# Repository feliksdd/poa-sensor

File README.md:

# POA-Sensor

Kabelgebundener Einstrahlungssensor mit KXOB25-14X1F-Referenzzelle, Präzisionsshunt, Zelltemperaturmessung und ADS1115. Ein Sensor wird über maximal 3 m Kabel von einem [PanelLog](https://github.com/feliksdd/panellog) versorgt und per I²C ausgelesen. Der Sensor wird parallel zur PV-Modulebene und möglichst unverschattet montiert.

| Datei | Inhalt |
|---|---|
| [KiCad-Projekt](hardware/poa-sensor.kicad_pro) · [Schaltplan](hardware/poa-sensor.kicad_sch) | Elektrische Quelle |
| [PCB](hardware/poa-sensor.kicad_pcb) | Layout mit Kradex-Kontur und integrierter Herstellerzeichnung |
| [PDF](hardware/poa-sensor.pdf) · [SVG](hardware/poa-sensor.svg) | Aktuelle Schaltplanansichten |
| [Stückliste](bom/bom.csv) | Bauteile, Bestellnummern und DNP-Bestückung |
| [Schaltung und Auslegung](docs/schaltung.md) | Messkanäle, Versorgung und I²C-Schnittstelle |
| [Mechanischer Aufbau](docs/aufbau.md) | Gehäusekontur, Zellkontakt und Montage |
| [Fertigung](docs/fertigung.md) | Bestückung und Fertigungsstand |

Das Schaltbild verwendet direkt gezeichnete Signalverbindungen, Spannungssymbole und zusammenhängende Funktionsgruppen. Das KiCad-Projekt verwendet KiCad 10. Die vorhandene PanelLog-Schnittstelle bleibt unverändert; eine eigene MCU oder Firmware ist nicht erforderlich.

Das PCB ist für **Kradex ZP60.60.40UJpH TM PC** mit transparentem Deckel angelegt. Das Layout enthält Leiterbahnen und konturgleiche GND-Flächen auf Ober- und Unterseite. Vor der Fertigung sind die offenen Punkte aus der Layoutprüfung zu klären. Herstellerzeichnungen, Freistellungen und Montagehöhe sind in [aufbau.md](docs/aufbau.md) beschrieben.

## Messprinzip und Umrechnung

Die KXOB25-14X1F arbeitet mit dem parallel geschalteten **1-Ω-Shunt RSH1** nahe am Kurzschluss. Auf diesem flachen Abschnitt der Zellkennlinie steigt der Strom näherungsweise proportional zur Einstrahlung in der Modulebene. Der ADS1115 misst die Shuntspannung differenziell an **AIN0–AIN1** mit getrennten Abgriffen an den beiden Shuntpads. Es gilt $I_\mathrm{Zelle} = U_\mathrm{SH}/R_\mathrm{SH}$. Bei einem PGA-Bereich von ±256 mV entspricht ein ADC-Count 7,8125 µV.

Bei 1.000 W/m², 25 °C und AM1.5 gibt ANYSOLAR typisch 58,6 mA Kurzschlussstrom an. Das entspricht am Shunt näherungsweise 58,6 mV bzw. 7.501 Counts. Aus dem typischen Temperaturkoeffizienten von +26,5 µA/K folgt die relative Korrektur $\alpha \approx 0{,}000452\,\mathrm{K}^{-1}$. [Datenblatt der KXOB25-14X1F](https://www.digikey.com/htmldatasheets/production/3648849/0/0/1/kxob25-14x1f-tr.pdf)

$$
G_\mathrm{POA} \approx 1000\,\frac{\mathrm W}{\mathrm{m^2}}\,
\frac{U_\mathrm{SH}-U_0}{58{,}6\,\mathrm{mV}}\,
\frac{1}{1+\alpha(T_\mathrm{Zelle}-25\,{}^\circ\mathrm C)}
$$

$U_0$ ist der bei lichtdicht abgedeckter Referenzzelle gemessene Offset. $T_\mathrm{Zelle}$ stammt vom NTC an der Zellrückseite. Eine offsetbereinigte Shuntspannung von 35,16 mV entspricht nominal 600 W/m² bei 25 °C bzw. 591 W/m² bei 60 °C.

Für absolute Werte den fertig montierten Sensor **mit Deckel** kalibrieren. Zuerst den Dunkeloffset $n_0$ in ADC-Counts erfassen. Dann bei stabiler Einstrahlung gleichzeitig den Sensorwert $n_\mathrm{ref}$, seine Zelltemperatur $T_\mathrm{ref}$ und die Einstrahlung $G_\mathrm{ref}$ einer kalibrierten Silizium-Referenzzelle messen. Beide Sensoren liegen in derselben Ebene. Die individuelle Empfindlichkeit ist

$$
S_{25} = \frac{n_\mathrm{ref}-n_0}{G_\mathrm{ref}\,[1+\alpha(T_\mathrm{ref}-25\,{}^\circ\mathrm C)]}
\quad \text{in Counts pro W/m².}
$$

Für die Auswertung in PanelLog gilt $G_\mathrm{POA}=(n-n_0)/(S_{25}[1+\alpha(T_\mathrm{Zelle}-25\,{}^\circ\mathrm C)])$. So gehen Zellstreuung, Shunt, ADC-Verstärkung und Deckeltransmission bei der Kalibriergeometrie in den Faktor ein. Den Einfluss des Deckels bei schrägem Lichteinfall separat durch Vergleichsmessungen prüfen. [Messkanäle und NTC-Auswertung](docs/schaltung.md)

## Werkzeuge

`bash tools/check_hardware.sh` prüft ERC, Netzliste und Stückliste. Die Ausgaben liegen in `build/kicad/` und werden nicht versioniert. `bash tools/export_schematic.sh` aktualisiert die PDF-/SVG-Ansichten unter `hardware/`.

Die verbindlichen Regeln für weitere Arbeiten stehen in [AGENTS.md](AGENTS.md).

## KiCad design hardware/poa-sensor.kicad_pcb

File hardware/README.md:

# Aktuelle Hardware: kabelgebundener POA, Revision 0.3

`poa-sensor.kicad_pro` / `poa-sensor.kicad_sch` sind das aktive Projekt: Referenzzelle, Shunt, Zell-NTC und I²C-ADC. Kabel und Versorgung sind in [architecture.md](../docs/architecture.md) festgelegt. Projektlokale Symbole einschließlich der festgelegten R/C-Kopien und Spannungssymbole vermeiden unterschiedliche Symbolbibliotheken zwischen KiCad 9 und 10; Footprints verweisen auf Standardbibliotheken bzw. `POA`.

Die früheren Dateien `poa-sensor-wired.*` wurden als Hauptprojekt übernommen. Die alte Batterie-/Funkversion heißt jetzt `poa-sensor-wireless-legacy.*`; auch ihre PCB-Datei trägt diesen Namen, damit sie nicht versehentlich mit dem neuen Hauptschaltplan zusammen bestellt wird. Frühere `.sch`-Bootstrap-Dateien und Normalisierungsskripte gehören ebenfalls zur Funkversion.

**Es existiert noch kein passendes kabelgebundenes PCB-Layout.** Das bestehende Layout-Template ist nur eine historische mechanische Vorlage. Für ein neues Layout Kelvin-Abgriffe, NTC-Zellkontakt, ruhige analoge Masse, Kabel-/ESD-Platzierung, Zugentlastung und optisches Fenster neu prüfen. Keine Fertigungsfreigabe aus einem ERC-Ergebnis ableiten.

Prüfen: `bash tools/review_hardware.sh`. Die Ausgabe liegt in `review_2026-11-10/`; der Netlist-Check prüft ADC-Pins, Kabelbelegung, ESD-Pins und Versorgungsdomänen. Für Montage-/Messhinweise siehe [Schaltplanrevision](../docs/wired_revision_2026-11-10.md).

Der Hauptschaltplan ist nach Referenzzelle/Kelvin-Filter, Temperatur-/Versorgungsteilern, ADC, I²C/Kabel/ESD sowie Versorgung/Abblockung angeordnet. Die Signale sind direkt verdrahtet; Labels dienen nur der Benennung. Die optionale Pufferbeschaltung liegt sichtbar parallel zu den Direktbrücken.

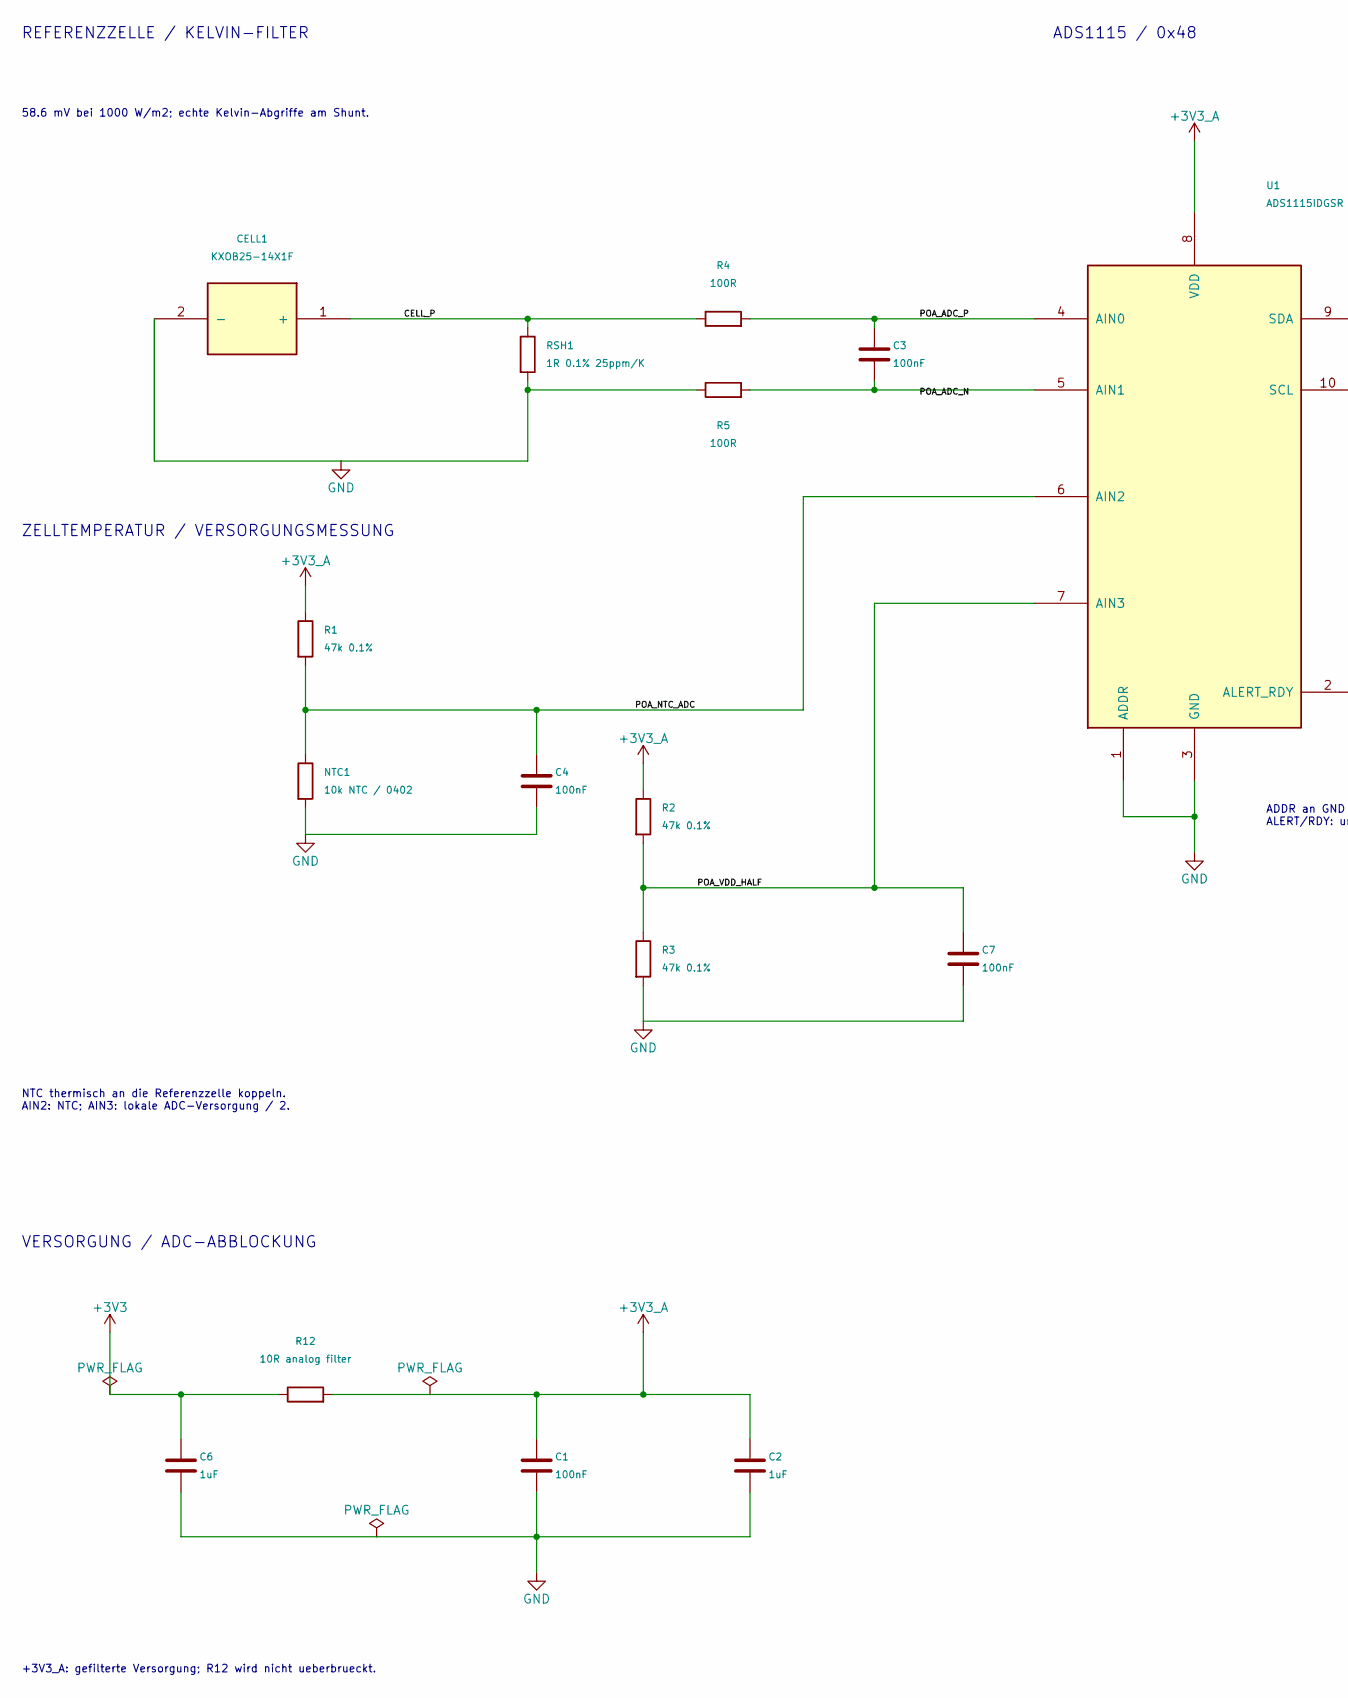
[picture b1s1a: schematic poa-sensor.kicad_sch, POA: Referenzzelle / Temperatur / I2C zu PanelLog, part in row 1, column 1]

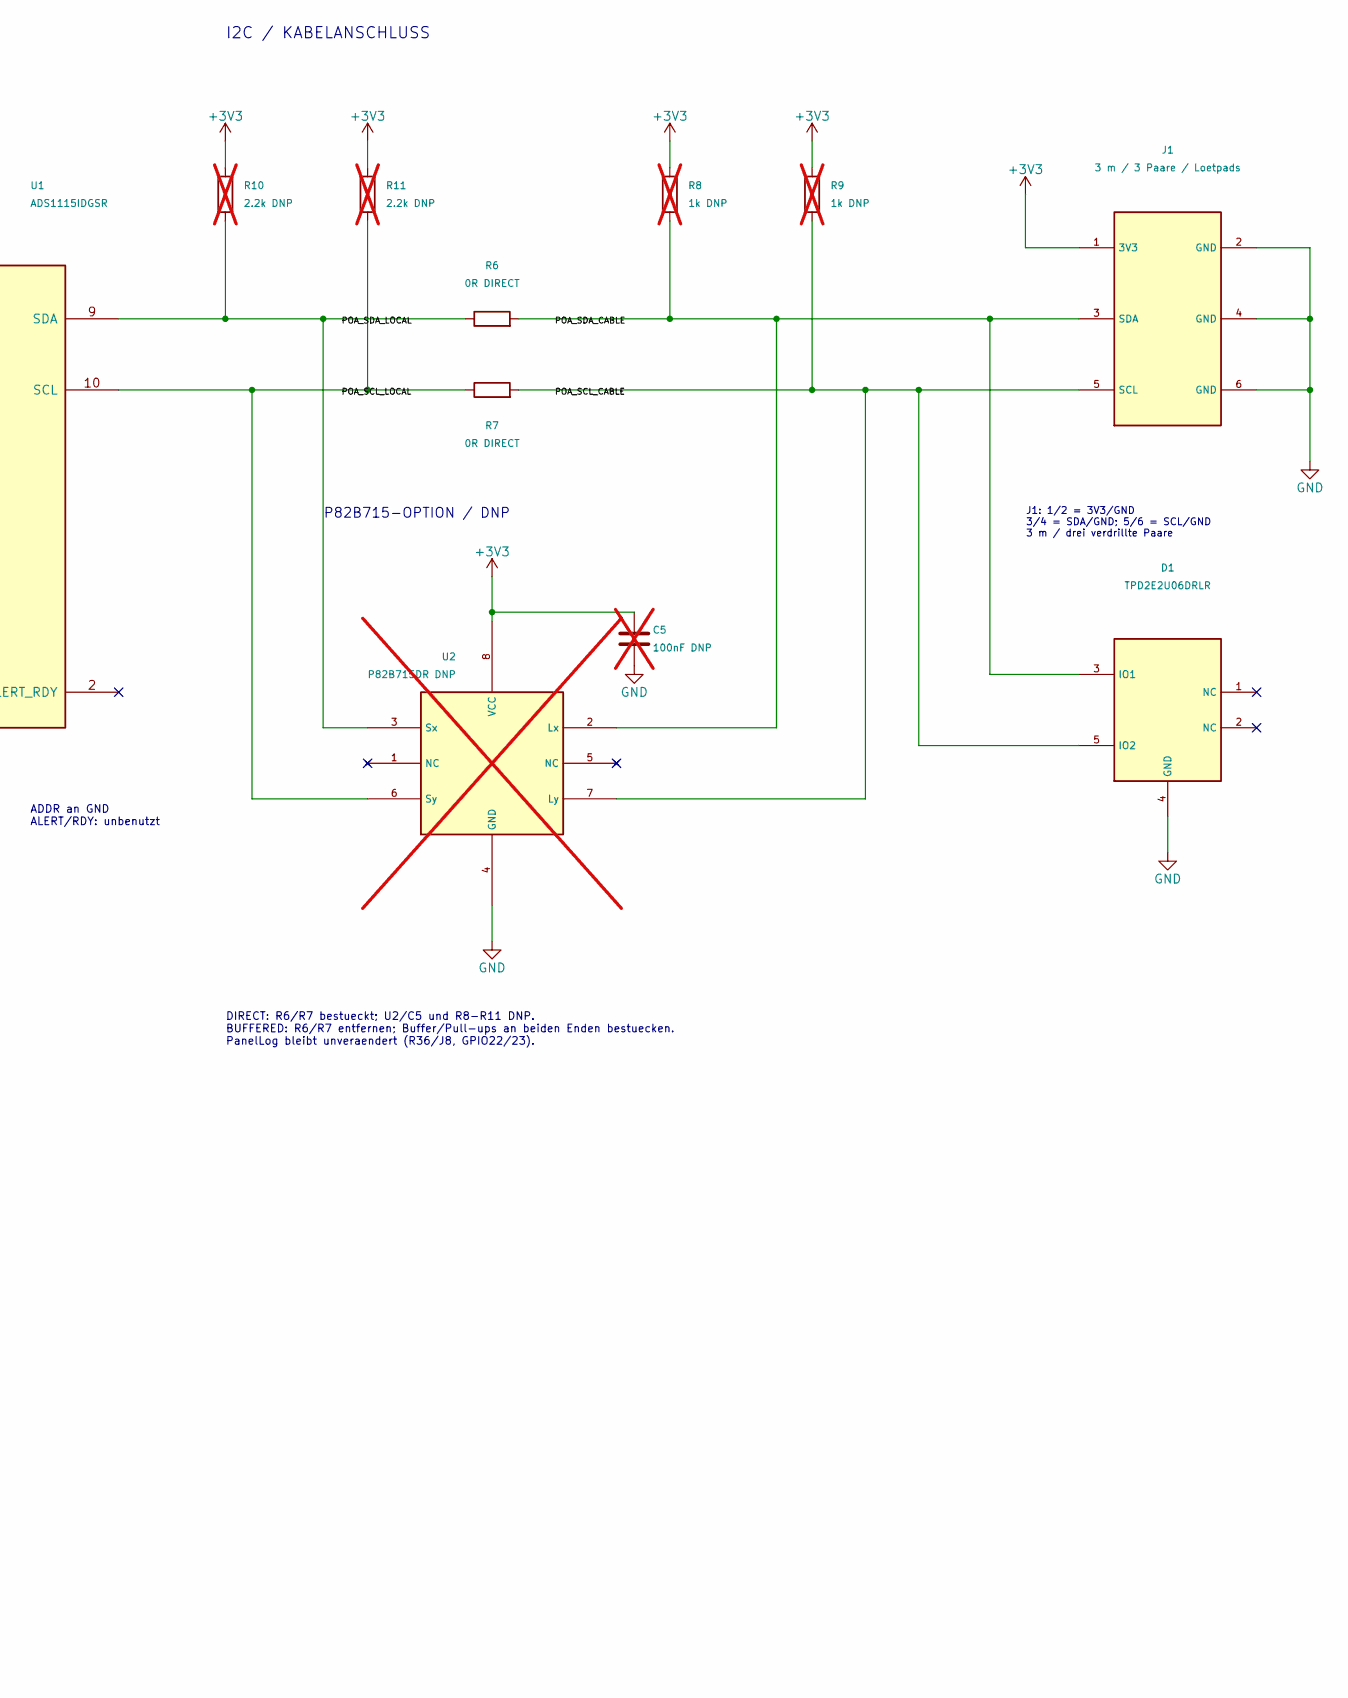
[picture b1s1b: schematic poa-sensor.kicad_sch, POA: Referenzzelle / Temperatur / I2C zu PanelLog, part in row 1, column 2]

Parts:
C1, C3, C4, C7: 100nF; C_0603_1608Metric; MPN CC0603KRX7R9BB104; LCSC C14663
C2, C6: 1uF; C_0805_2012Metric; MPN CL21B105KBFNNNE; LCSC C28323
C5: 100nF DNP; C_0603_1608Metric; MPN CC0603KRX7R9BB104; LCSC C14663; not fitted
CELL1: KXOB25-14X1F; MPN KXOB25-14X1F-TR
D1: TPD2E2U06DRLR; SOT-553; MPN TPD2E2U06DRLR; LCSC C1972959
J1: 3 m / 3 Paare / Loetpads; POA_Cable_6pad
NTC1: 10k NTC / 0402; R_0402_1005Metric; MPN NTCG103JF103FT1; LCSC C209959
R1, R2, R3: 47k 0.1%; R_0603_1608Metric; MPN AR03BTCX4702; LCSC C2828645
R4, R5: 100R; R_0603_1608Metric; MPN 0603WAF1000T5E; LCSC C22775
R6, R7: 0R DIRECT; R_0603_1608Metric; MPN 0603WAF0000T5E; LCSC C21189
R8, R9: 1k DNP; R_0603_1608Metric; MPN 0603WAF1001T5E; LCSC C21190; not fitted
R10, R11: 2.2k DNP; R_0603_1608Metric; MPN 0603WAF2201T5E; LCSC C4190; not fitted
R12: 10R analog filter; R_0603_1608Metric; MPN 0603WAF100JT5E; LCSC C22859
RSH1: 1R 0.1% 25ppm/K; R_0805_2012Metric; MPN RT0805BRD071RL; LCSC C865286
U1: ADS1115IDGSR; MSOP-10_3x3mm_P0.5mm; MPN ADS1115IDGSR; LCSC C37593
U2: P82B715DR DNP; SOIC-8_3.9x4.9mm_P1.27mm; MPN P82B715DR; LCSC C2649394; not fitted

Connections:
+3V3: C5.1, C6.1, J1.1 (3V3), R8.1, R9.1, R10.1, R11.1, R12.1, U2.8 (VCC)
+3V3_A: C1.1, C2.1, R1.1, R2.1, R12.2, U1.8 (VDD)
/CELL_P: CELL1.1 (+), R4.1, RSH1.1
/POA_ADC_N: C3.2, R5.2, U1.5 (AIN1)
/POA_ADC_P: C3.1, R4.2, U1.4 (AIN0)
/POA_NTC_ADC: C4.1, NTC1.1, R1.2, U1.6 (AIN2)
/POA_SCL_CABLE: D1.5 (IO2), J1.5 (SCL), R7.2, R9.2, U2.7 (Ly)
/POA_SCL_LOCAL: R7.1, R11.2, U1.10 (SCL), U2.6 (Sy)
/POA_SDA_CABLE: D1.3 (IO1), J1.3 (SDA), R6.2, R8.2, U2.2 (Lx)
/POA_SDA_LOCAL: R6.1, R10.2, U1.9 (SDA), U2.3 (Sx)
/POA_VDD_HALF: C7.1, R2.2, R3.1, U1.7 (AIN3)
GND: C1.2, C2.2, C4.2, C5.2, C6.2, C7.2, CELL1.2 (-), D1.4 (GND), J1.2 (GND), J1.4 (GND), J1.6 (GND), NTC1.2, R3.2, R5.1, RSH1.2, U1.1 (ADDR), U1.3 (GND), U2.4 (GND)

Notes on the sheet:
NTC thermisch an die Referenzzelle koppeln. AIN2: NTC; AIN3: lokale ADC-Versorgung / 2.
VERSORGUNG / ADC-ABBLOCKUNG
P82B715-OPTION / DNP
J1: 1/2 = 3V3/GND 3/4 = SDA/GND; 5/6 = SCL/GND 3 m / drei verdrillte Paare
REFERENZZELLE / KELVIN-FILTER
ADS1115 / 0x48
DIRECT: R6/R7 bestueckt; U2/C5 und R8-R11 DNP. BUFFERED: R6/R7 entfernen; Buffer/Pull-ups an beiden Enden bestuecken. PanelLog bleibt unveraendert (R36/J8, GPIO22/23).
58.6 mV bei 1000 W/m2; echte Kelvin-Abgriffe am Shunt.
ZELLTEMPERATUR / VERSORGUNGSMESSUNG
ADDR an GND ALERT/RDY: unbenutzt
I2C / KABELANSCHLUSS
+3V3_A: gefilterte Versorgung; R12 wird nicht ueberbrueckt.

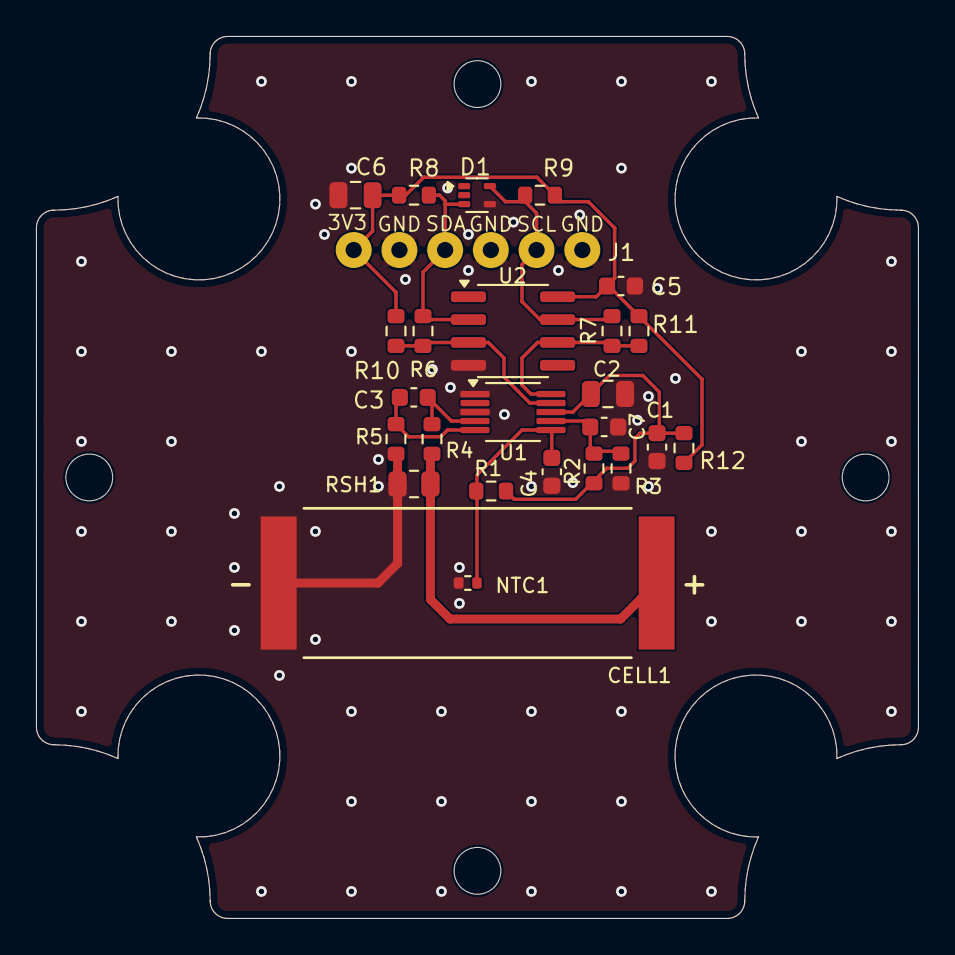
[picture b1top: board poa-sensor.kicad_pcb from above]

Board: 2 copper layers, 49.0 x 49.0 mm, 30 parts (0 on the bottom side), 12 nets.

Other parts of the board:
H1, H2, H3, H4: NPTH 2.6mm; Kradex_ZP60_MountingHole_2.6mm

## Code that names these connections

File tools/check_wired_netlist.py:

#!/usr/bin/env python3
"""Check the electrical interface in a native KiCad XML netlist, using stdlib only."""
import argparse, csv, json
from pathlib import Path
import xml.etree.ElementTree as ET

parser=argparse.ArgumentParser()
parser.add_argument('netlist',type=Path)
parser.add_argument('--host',action='store_true')
parser.add_argument('--bom',type=Path)
args=parser.parse_args()
root=ET.parse(args.netlist).getroot()
components={c.get('ref'):c for c in root.findall('./components/comp')}
nets={}
for net in root.findall('./nets/net'):
    name=net.get('name').lstrip('/')
    for n in net.findall('node'):
        nets[(n.get('ref'),n.get('pin'))]=name

def expect(ref,pin,name):
    actual=nets.get((ref,str(pin)))
    if actual!=name:
        raise SystemExit(f'{ref}.{pin}: expected {name}, got {actual}')

def populated(ref,yes):
    c=components[ref]
    dnp=any(p.get('name')=='dnp' for p in c.findall('property'))
    if dnp==yes:raise SystemExit(f'{ref}: incorrect DNP state')

if args.host:
    # PanelLog interface: supply through R36 and local pullups.
    for pin,name in {2:'GND',3:'POA_SDA_CABLE',4:'GND',5:'POA_SCL_CABLE',6:'GND'}.items():expect('J8',pin,name)
    expect('R36',1,'+3V3')
    if nets.get(('J8','1'))!=nets.get(('R36','2')):raise SystemExit('J8.1 must be fed through R36')
    if components['R36'].findtext('value')!='0R':raise SystemExit('R36 must remain 0R')
    expect('U3',20,'POA_SDA_MCU');expect('U3',21,'POA_SCL_MCU')
    for ref,name in [('R30','POA_SDA_MCU'),('R31','POA_SCL_MCU')]:
        expect(ref,1,'+3V3');expect(ref,2,name);populated(ref,True)
        if components[ref].findtext('value')!='2.2k':raise SystemExit(f'{ref}: expected 2.2k')
    for ref in ['R34','R35','U4','C26']:populated(ref,False)
    for ref in ['R30','R31','R32','R33','R36']:populated(ref,True)
    expect('D3',3,'POA_SDA_CABLE');expect('D3',4,'GND');expect('D3',5,'POA_SCL_CABLE')
else:
    for pin,name in {1:'+3V3',2:'GND',3:'POA_SDA_CABLE',4:'GND',5:'POA_SCL_CABLE',6:'GND'}.items():expect('J1',pin,name)
    for pin,name in {1:'GND',3:'GND',4:'POA_ADC_P',5:'POA_ADC_N',6:'POA_NTC_ADC',7:'POA_VDD_HALF',8:'+3V3_A',9:'POA_SDA_LOCAL',10:'POA_SCL_LOCAL'}.items():expect('U1',pin,name)
    expect('D1',3,'POA_SDA_CABLE');expect('D1',4,'GND');expect('D1',5,'POA_SCL_CABLE')
    expect('R12',1,'+3V3');expect('R12',2,'+3V3_A')
    expect('CELL1',1,'CELL_P');expect('CELL1',2,'GND')
    expect('RSH1',1,'CELL_P');expect('RSH1',2,'GND')
    for ref,n in [('R4','POA_ADC_P'),('R5','POA_ADC_N')]:expect(ref,2,n)
    expect('R1',1,'+3V3_A');expect('R1',2,'POA_NTC_ADC')
    expect('NTC1',1,'POA_NTC_ADC');expect('NTC1',2,'GND')
    for ref in ['U2','R8','R9','R10','R11','C5']:populated(ref,False)
    for ref in ['R6','R7','U1','D1','NTC1','RSH1']:populated(ref,True)
    if '0805' not in components['RSH1'].findtext('footprint'):raise SystemExit('Shunt package must be 0805')
    if any(r in components for r in ['BT1','Y1','NTC2']):raise SystemExit('Unexpected battery, clock or second temperature channel')
if args.bom:
    with args.bom.open() as f:rows=list(csv.DictReader(f))
    by_ref={r['Ref']:r for r in rows}
    if set(by_ref)!=set(components):raise SystemExit('BOM designators differ from schematic')
    for ref,c in components.items():
        fields={f.get('name'):f.text or '' for f in c.findall('./fields/field')}
        for field in ['LCSC','MPN']:
            if by_ref[ref][field]!=fields.get(field,''):raise SystemExit(f'{ref}: BOM {field} mismatch')
        for column,tag in [('Value','value'),('Footprint','footprint')]:
            if by_ref[ref][column]!=(c.findtext(tag) or ''):raise SystemExit(f'{ref}: BOM {column} mismatch')
print(json.dumps({'kind':'PanelLog host' if args.host else 'POA','components':len(components),'checked':'connector, ADC, supply, ESD, default assembly and optional BOM','result':'PASS'},indent=2))
